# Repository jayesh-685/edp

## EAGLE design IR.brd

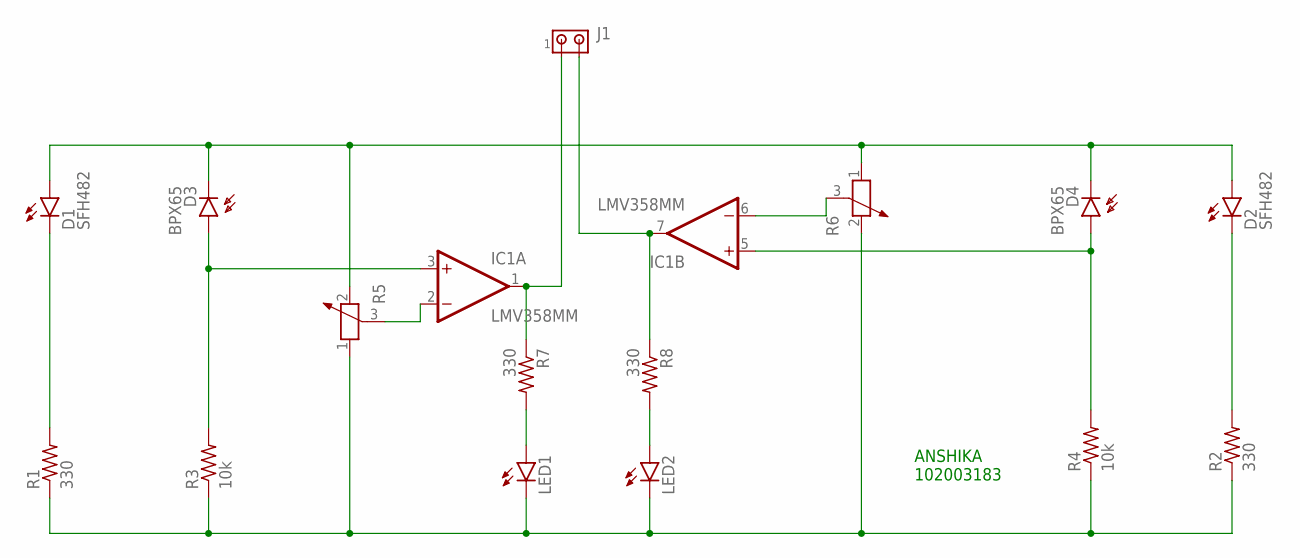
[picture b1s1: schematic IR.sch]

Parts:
D1, D2: SFH482
D3, D4: BPX65
IC1: LMV358MM; MSOP08
J1: MTA02-100; 10X02MTA
LED1, LED2: LED3MM
R1, R2, R7, R8: 330; 0207/10
R3, R4: 10k; 0207/10
R5, R6: POTENTIOMETER_PT-10S; PT-10S

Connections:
unnamed: D1.K (C), R1.2
unnamed: D3.A, IC1.3 (+IN), R3.2
unnamed: D1.A, D2.A, D3.K (C), D4.K (C), R5.2, R6.1
unnamed: D4.A, IC1.5 (+IN), R4.2
unnamed: D2.K (C), R2.2
unnamed: LED1.K (C), LED2.K (C), R1.1, R2.1, R3.1, R4.1, R5.1, R6.2
unnamed: IC1.2 (-IN), R5.3
unnamed: LED2.A, R8.2
unnamed: LED1.A, R7.2
unnamed: IC1.1 (OUT), J1.1, R7.1
unnamed: IC1.7 (OUT), J1.2, R8.1
unnamed: IC1.6 (-IN), R6.3
V+: IC1.8 (V+)
V-: IC1.4 (V-)

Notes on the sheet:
ANSHIKA 102003183

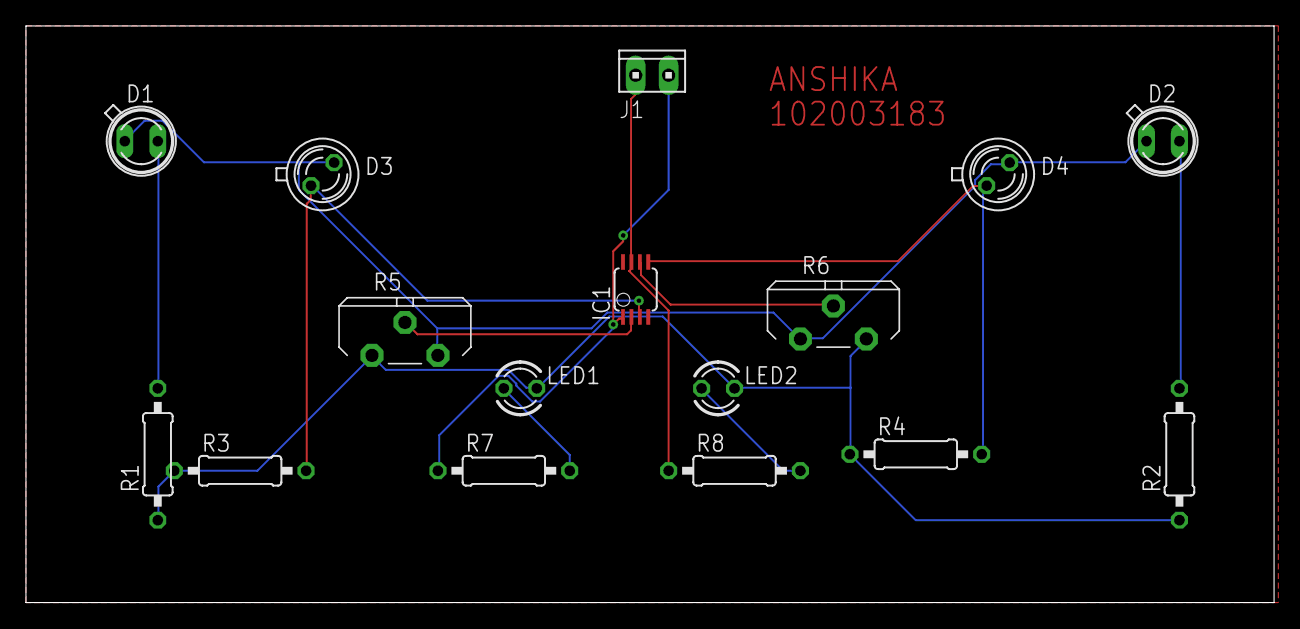
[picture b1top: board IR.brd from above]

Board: 2 copper layers, 96.2 x 44.4 mm, 16 parts (0 on the bottom side), 12 nets.

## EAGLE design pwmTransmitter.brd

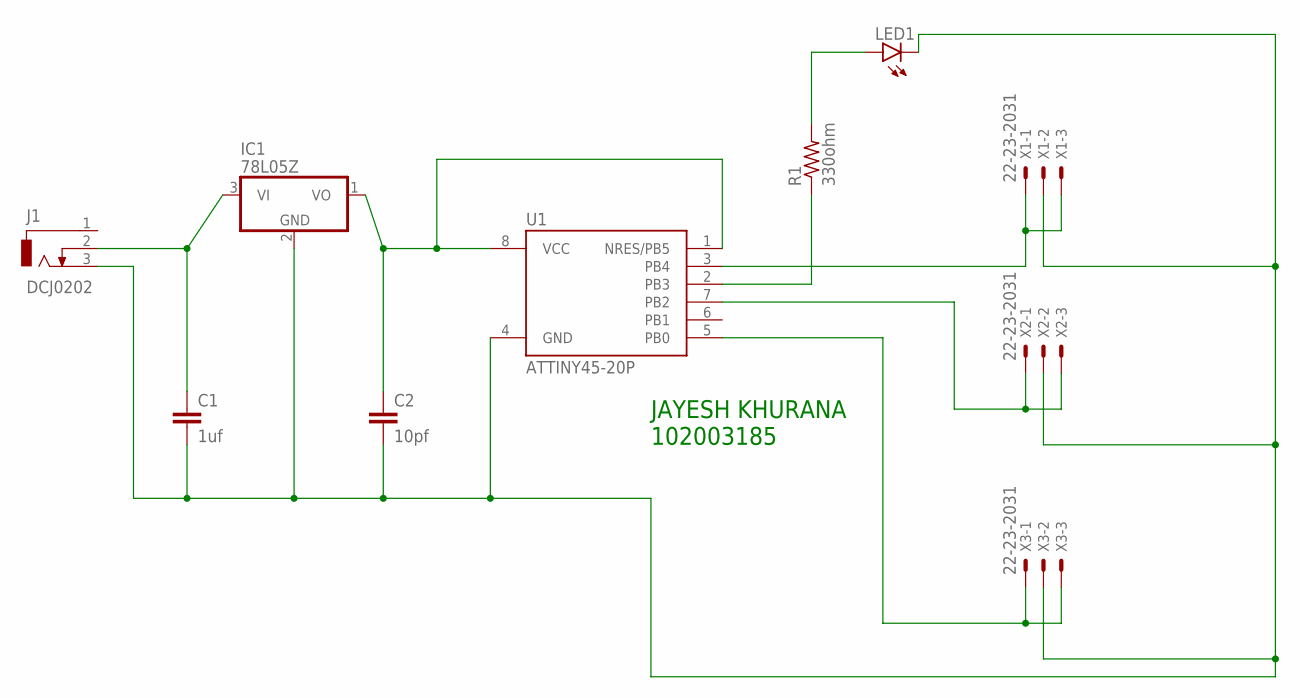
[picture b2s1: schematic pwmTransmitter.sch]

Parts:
C1: 1uf; C2.5-2
C2: 10pf; C2.5-2
IC1: 78L05Z; TO92
J1: DCJ0202
LED1: LED3MM
R1: 330ohm; 0207/10
U1: ATTINY45-20P; PDIP08_300MIL
X1, X2, X3: 22-23-2031

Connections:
unnamed: C1.1, IC1.3 (VI), J1.2
unnamed: C1.2, C2.2, IC1.2 (GND), J1.3, LED1.K (C), U1.4 (GND), X1.2, X2.2, X3.2
unnamed: C2.1, IC1.1 (VO), U1.1 (NRES/PB5), U1.8 (VCC)
unnamed: R1.1, U1.2 (PB3)
unnamed: U1.3 (PB4), X1.1, X1.3
unnamed: U1.7 (PB2), X2.1, X2.3
unnamed: U1.5 (PB0), X3.1, X3.3
unnamed: LED1.A, R1.2

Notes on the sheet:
JAYESH KHURANA 102003185

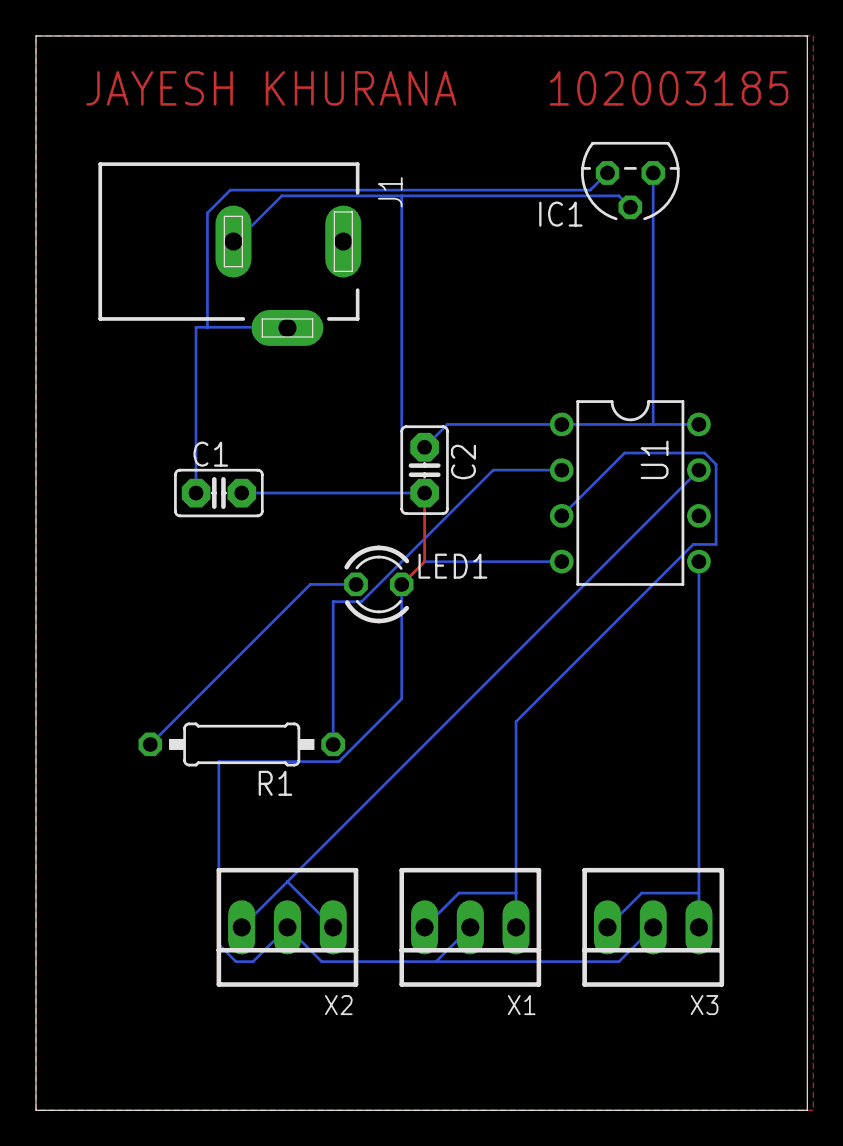
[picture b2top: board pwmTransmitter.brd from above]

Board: 2 copper layers, 42.9 x 59.7 mm, 10 parts (0 on the bottom side), 8 nets.

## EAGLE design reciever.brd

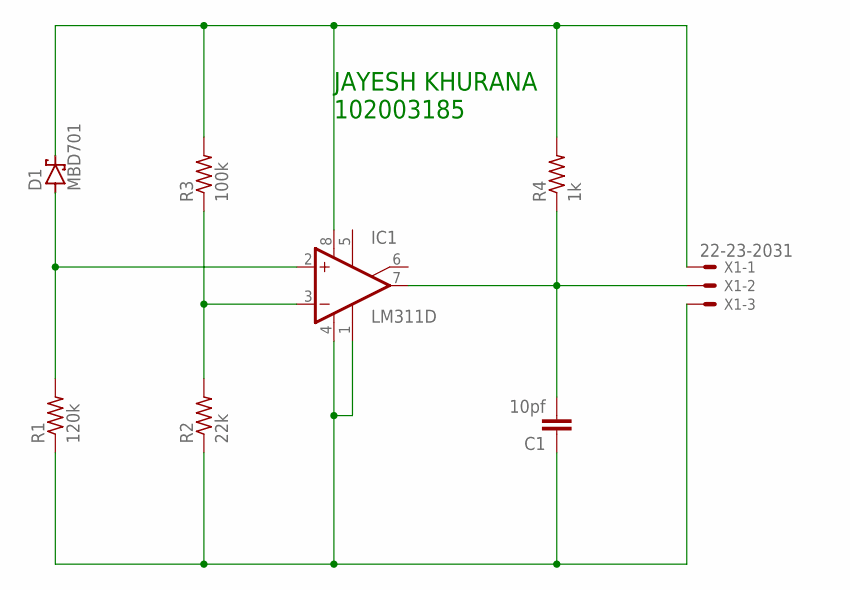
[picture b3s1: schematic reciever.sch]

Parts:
C1: 10pf; C2.5-2
D1: MBD701; TO92H
IC1: LM311D; SO08
R1: 120k; 0207/10
R2: 22k; 0207/10
R3: 100k; 0207/10
R4: 1k; 0207/10
X1: 22-23-2031

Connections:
unnamed: D1.2 (C), IC1.8 (V+), R3.2, R4.2, X1.1
unnamed: C1.1, IC1.1 (GND), IC1.4 (V-), R1.1, R2.1, X1.3
unnamed: D1.1 (A), IC1.2 (+IN), R1.2
unnamed: IC1.3 (-IN), R2.2, R3.1
unnamed: C1.2, IC1.7 (OUT), R4.1, X1.2

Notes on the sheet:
JAYESH KHURANA 102003185

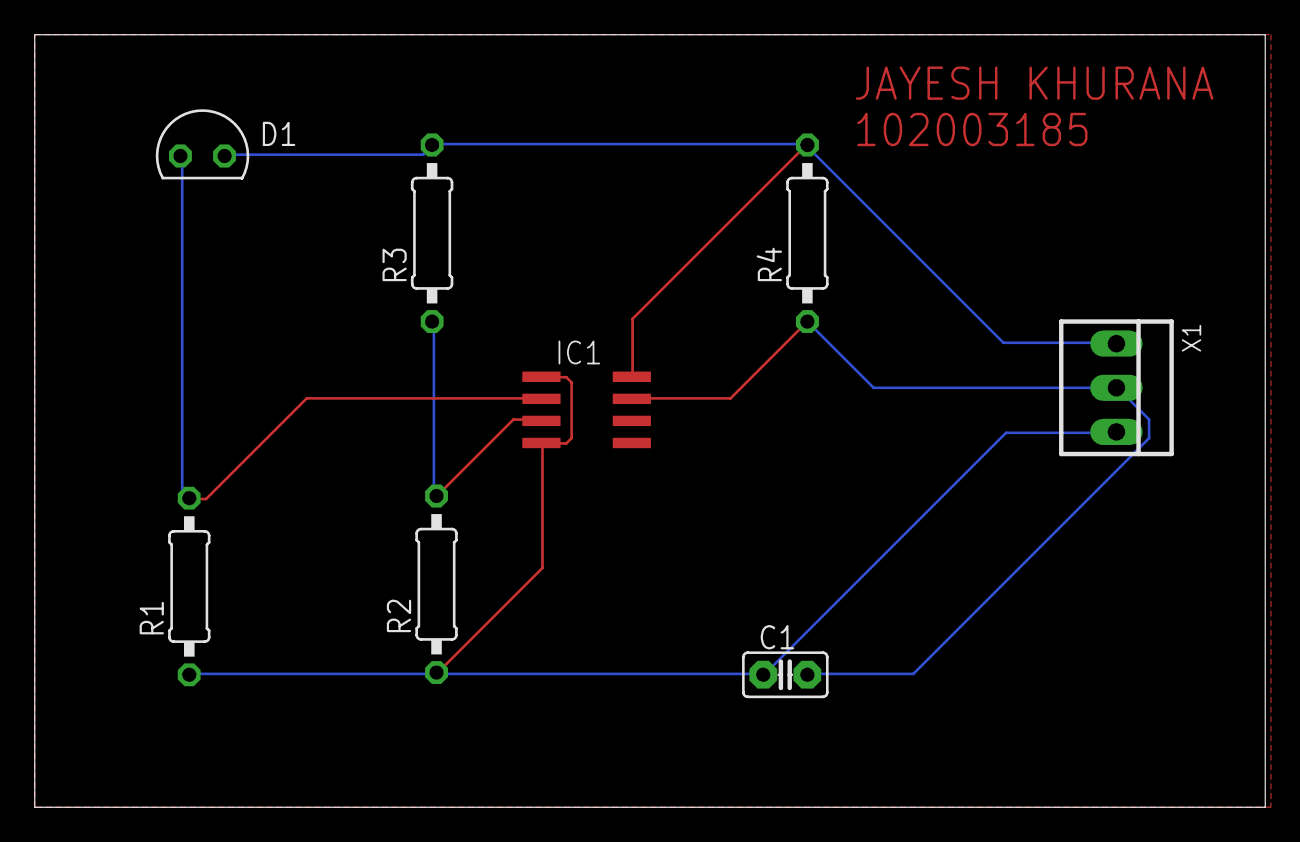
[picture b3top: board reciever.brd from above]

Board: 2 copper layers, 70.8 x 44.4 mm, 8 parts (0 on the bottom side), 5 nets.
